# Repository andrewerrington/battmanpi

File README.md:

# BattManPi
A project to redesign Stefan Vorkoetter's BattMan II for Raspberry Pi:  
http://www.stefanv.com/electronics/battman2.html

BattMan II is a computer-controlled battery manager which can be used
to charge and discharge common types of rechargeable batteries.

The original project used a Borland C++ program under Windows to drive
the hardware through the PC LPT port.  These days LPT ports are rare, and
no-one has updated the software to use another interface method such as
a USB GPIO module.

There are three aspects to this project.  First, redesign the circuit to
operate with the Raspberry Pi 3.3V GPIO levels.  Second, lay out a new
PCB for the new circuit.  Third, translate the Borland C++ code to
something that will run on the Pi.

The first phase is addressed by the schematic found in the project files
here.  The schematic was drawn using KiCAD, which was then used to do
the PCB artwork for the second phase.  For the third phase, the original
C++ code has been converted to Python with a TKinter GUI.  Permission has
been granted to release the new code under the GPL.  This does not
affect the license of the original code.

At the time of writing the schematic, PCB artwork, and software are ready
for testing.  The PCB has not been fabricated, so the circuit and the
software have not been tested.  I hope to have time to do this in April
or May 2017.

The original design is copyright Stefan Vorkoetter 2007.

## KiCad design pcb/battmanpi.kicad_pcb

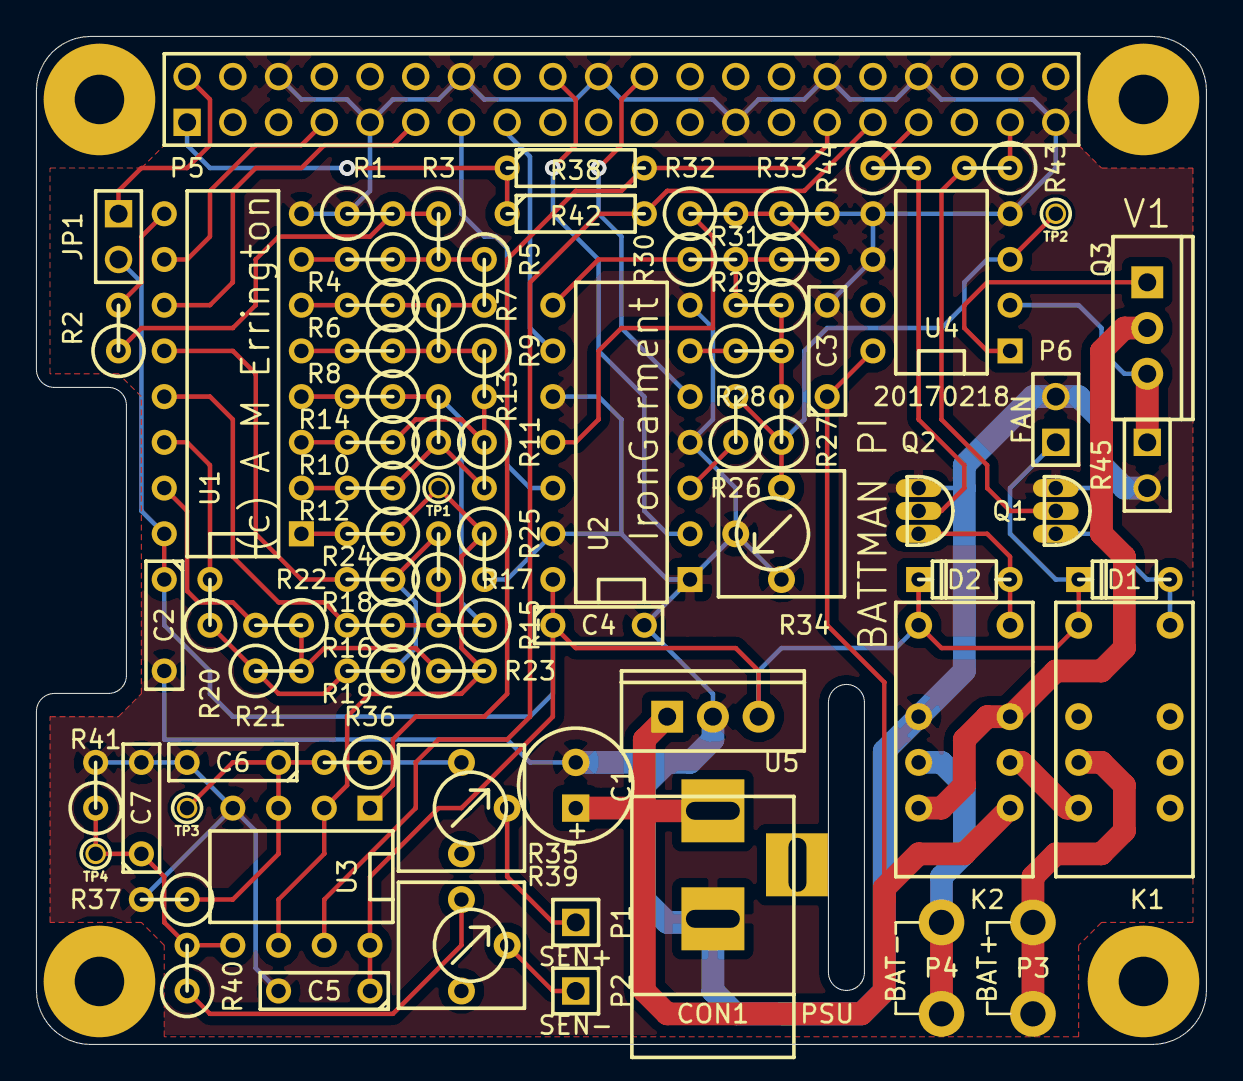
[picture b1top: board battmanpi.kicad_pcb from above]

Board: 2 copper layers, 65.0 x 56.0 mm, 80 parts (0 on the bottom side), 63 nets.

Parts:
C1: 10u; C1V7
C2, C3, C4, C5, C6, C7: 0.1u; C2
CON1: PSU; BARREL_JACK
D1, D2: 1N914; D3S
JP1: 5V link; PIN_ARRAY_2X1
K1, K2: TX2-5V; RELAY_FORMC
P1: SEN+; PIN_ARRAY_1
P2: SEN-; PIN_ARRAY_1
P3: BAT+; 635mmspade
P4: BAT-; 635mmspade
P5: Raspberry Pi; PIN_ARRAY_20X2
P6: FAN; PIN_ARRAY_2X1
Q1, Q2: 2N3904; TO92bulk
Q3: TIP120; TO220V
R1, R2, R4, R6, R8, R10, R12, R14, R16, R18, R20, R22, R24, R26, R28, R30, R32, R33, R37, R41: 20k; R1
R3, R5, R7, R9, R11, R13, R15, R17, R19, R21, R23, R27, R29, R31: 10k; R1
R25: 15k; R1
R34: 1k; 6mmSQ
R35, R39: 10k; 6mmSQ
R36, R40: 100k; R1
R38, R42: 4.7k; R3
R43, R44: 1k; R1
R45: 0.1 2W; PIN_ARRAY_2X1
TP1, TP2, TP3, TP4: TST; PINTST
U1: 74HCT4040; DIP-16__300
U2: 74HCT125; DIP-14__300
U3: LM393; DIP-8__300
U4: LM358; DIP-8__300
U5: 7805; TO220V
mounting_hole: VAL**; mounting_hole
mounting_hole#2, mounting_hole#3, mounting_hole#4: VAL**; mounting_hole

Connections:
+3.3V: P5.1, R38.1, R42.1
+5V: C2.1, C4.1, C5.1, D1.2, D2.2, JP1.2, K1.1, K2.1, P6.1, U1.16, U2.14, U3.8, U5.3
+24V: C1.1, C3.1, CON1.1, K2.8, U4.8, U5.1
/CNCT: P5.37, R43.1
/D0: P5.13, U2.12
/D1: P5.15, U2.9
/D2: P5.22, U2.5
/D3: P5.18, U2.2
/INCR: P5.7, U1.10
/MODE: P5.33, R44.1
/VDAC: R23.2, R24.1, R25.1, TP1.1, U3.2, U3.6
/VDAC<B+: P5.29, R38.2, U3.1
/VDAC<B-: P5.31, R42.2, U3.7
/ZERO: P5.11, U1.11
GND: C1.2, C2.2, C3.2, C4.2, C5.2, C6.2, C7.2, CON1.2, K2.3, P5.6, P5.9, P5.14, P5.20, P5.25, P5.30, P5.34, P5.39, P6.2, Q1.1, Q2.1, R1.1, R25.2, R33.2, R34.1, R34.2, R37.2, R41.2, R45.2, U1.8, U2.1, U2.4, U2.7, U2.10, U2.13, U3.4, U4.4, U4.5, U4.6, U5.2
unnamed: R39.1, R40.1
unnamed: P2.1, R39.2
unnamed: R35.1, R36.1
unnamed: P1.1, R35.2
unnamed: R12.2, U1.2
unnamed: R4.2, U1.7
unnamed: R6.2, U1.6
unnamed: R8.2, U1.5
unnamed: R10.2, U1.3
unnamed: R14.2, U1.4
unnamed: R16.2, U1.13
unnamed: R18.2, U1.12
unnamed: R9.2, R10.1, R11.1
unnamed: R7.2, R8.1, R9.1
unnamed: R5.2, R6.1, R7.1
unnamed: R3.2, R4.1, R5.1
unnamed: R1.2, R2.1, R3.1
unnamed: R2.2, U1.9
unnamed: D1.1, K1.12, Q1.3
unnamed: K2.4, P4.1
unnamed: Q1.2, R43.2
unnamed: K1.4, P3.1
unnamed: K1.5, K2.9
unnamed: Q2.2, R44.2
unnamed: R20.2, U1.14
unnamed: R22.2, U1.15
unnamed: R24.2, U1.1
unnamed: C6.1, R36.2, R37.1, TP3.1, U3.3
unnamed: D2.1, K2.12, Q2.3
unnamed: K2.5, K2.10, Q3.2
unnamed: JP1.1, P5.2
unnamed: C7.1, R40.2, R41.1, TP4.1, U3.5
unnamed: R13.2, R14.1, R15.1
unnamed: R11.2, R12.1, R13.1
unnamed: R17.2, R18.1, R19.1
unnamed: R21.2, R22.1, R23.1
unnamed: R15.2, R16.1, R17.1
unnamed: R26.2, R27.1, R34.3, TP2.1, U4.3
unnamed: Q3.3, R45.1, U4.2
unnamed: Q3.1, U4.1
unnamed: R31.2, R32.2, R33.1
unnamed: R26.1, U2.3
unnamed: R28.1, U2.6
unnamed: R27.2, R28.2, R29.1
unnamed: R30.1, U2.8
unnamed: R29.2, R30.2, R31.1
unnamed: R32.1, U2.11
unnamed: R19.2, R20.1, R21.1

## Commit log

2016-12-19 First commit (schematic and BOM)
2016-12-19 Added a README file
2017-01-07 Added a draft of the PCB layout.
2017-01-07 Updated schematic.
2017-01-08 Some screenshots of GUI under development.
2017-02-01 Create LICENCE
2017-02-01 First draft of application framework.
2017-02-01 KiCAD pcb files
2017-02-02 Fixing omission of start.py
2017-02-02 Moved GIF icons into inline base64 encoded strings. Changed dialogs to non-resizable. Fixed range of charge/discharge slider (1-15, not 0-15).
2017-02-05 Implemented impedance check.
2017-02-06 All functions implemented. Next is bugfixing and testing.
2017-02-08 AutoCycle bug fixed.
2017-02-08 KiCad project file for PCB design
2017-02-08 Updated README file
2017-02-12 Added some KiCad library files
2017-02-13 Various bug fixes
2017-02-16 Updated schematic and PCB artwork.
2017-02-16 Cleaner PCB artwork
2017-02-18 Almost final PCB layout. All holes set to 0.8 or 1.0 mm (except special components and mounting). Next make traces slightly wider.
2017-02-19 Updated PCB layout
2017-02-19 Gerber files for PCB manufacture.
2017-02-20 Latest PCB.
2017-02-22 PCB release candidate
2017-02-22 Made ground lines a little thicker
2017-02-22 Updated hardware.py to match GPIO pins on new schematic
2017-02-22 Latest KiCad project files
2017-04-14 Update battmanpi.lst
    Added component lead spacing and identified trimmer pots.
